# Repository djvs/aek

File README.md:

# aek[2]

USB/QMK atmega32u4 pcb for M0115, M3501 and possibly others, with WS2812B addressable LED support.  

Released without warranty, use at your own risk.  

PRs & feedback welcome!

---

Dimensions: 437.896 x 141.732 mm

---

Keyboard-Layout-Editor of Matrix for Vial: http://www.keyboard-layout-editor.com/#/gists/c7bd3d0e6c43f816d1fdc86e6fad2cfd

Default keymap: 

In Vial:

Some Photos:

Shield: [![CC BY-SA 4.0][cc-by-sa-shield]][cc-by-sa]

This work is licensed under a
[Creative Commons Attribution-ShareAlike 4.0 International License][cc-by-sa].

[![CC BY-SA 4.0][cc-by-sa-image]][cc-by-sa]

[cc-by-sa]: http://creativecommons.org/licenses/by-sa/4.0/
[cc-by-sa-image]: https://licensebuttons.net/l/by-sa/4.0/88x31.png
[cc-by-sa-shield]: https://img.shields.io/badge/License-CC%20BY--SA%204.0-lightgrey.svg

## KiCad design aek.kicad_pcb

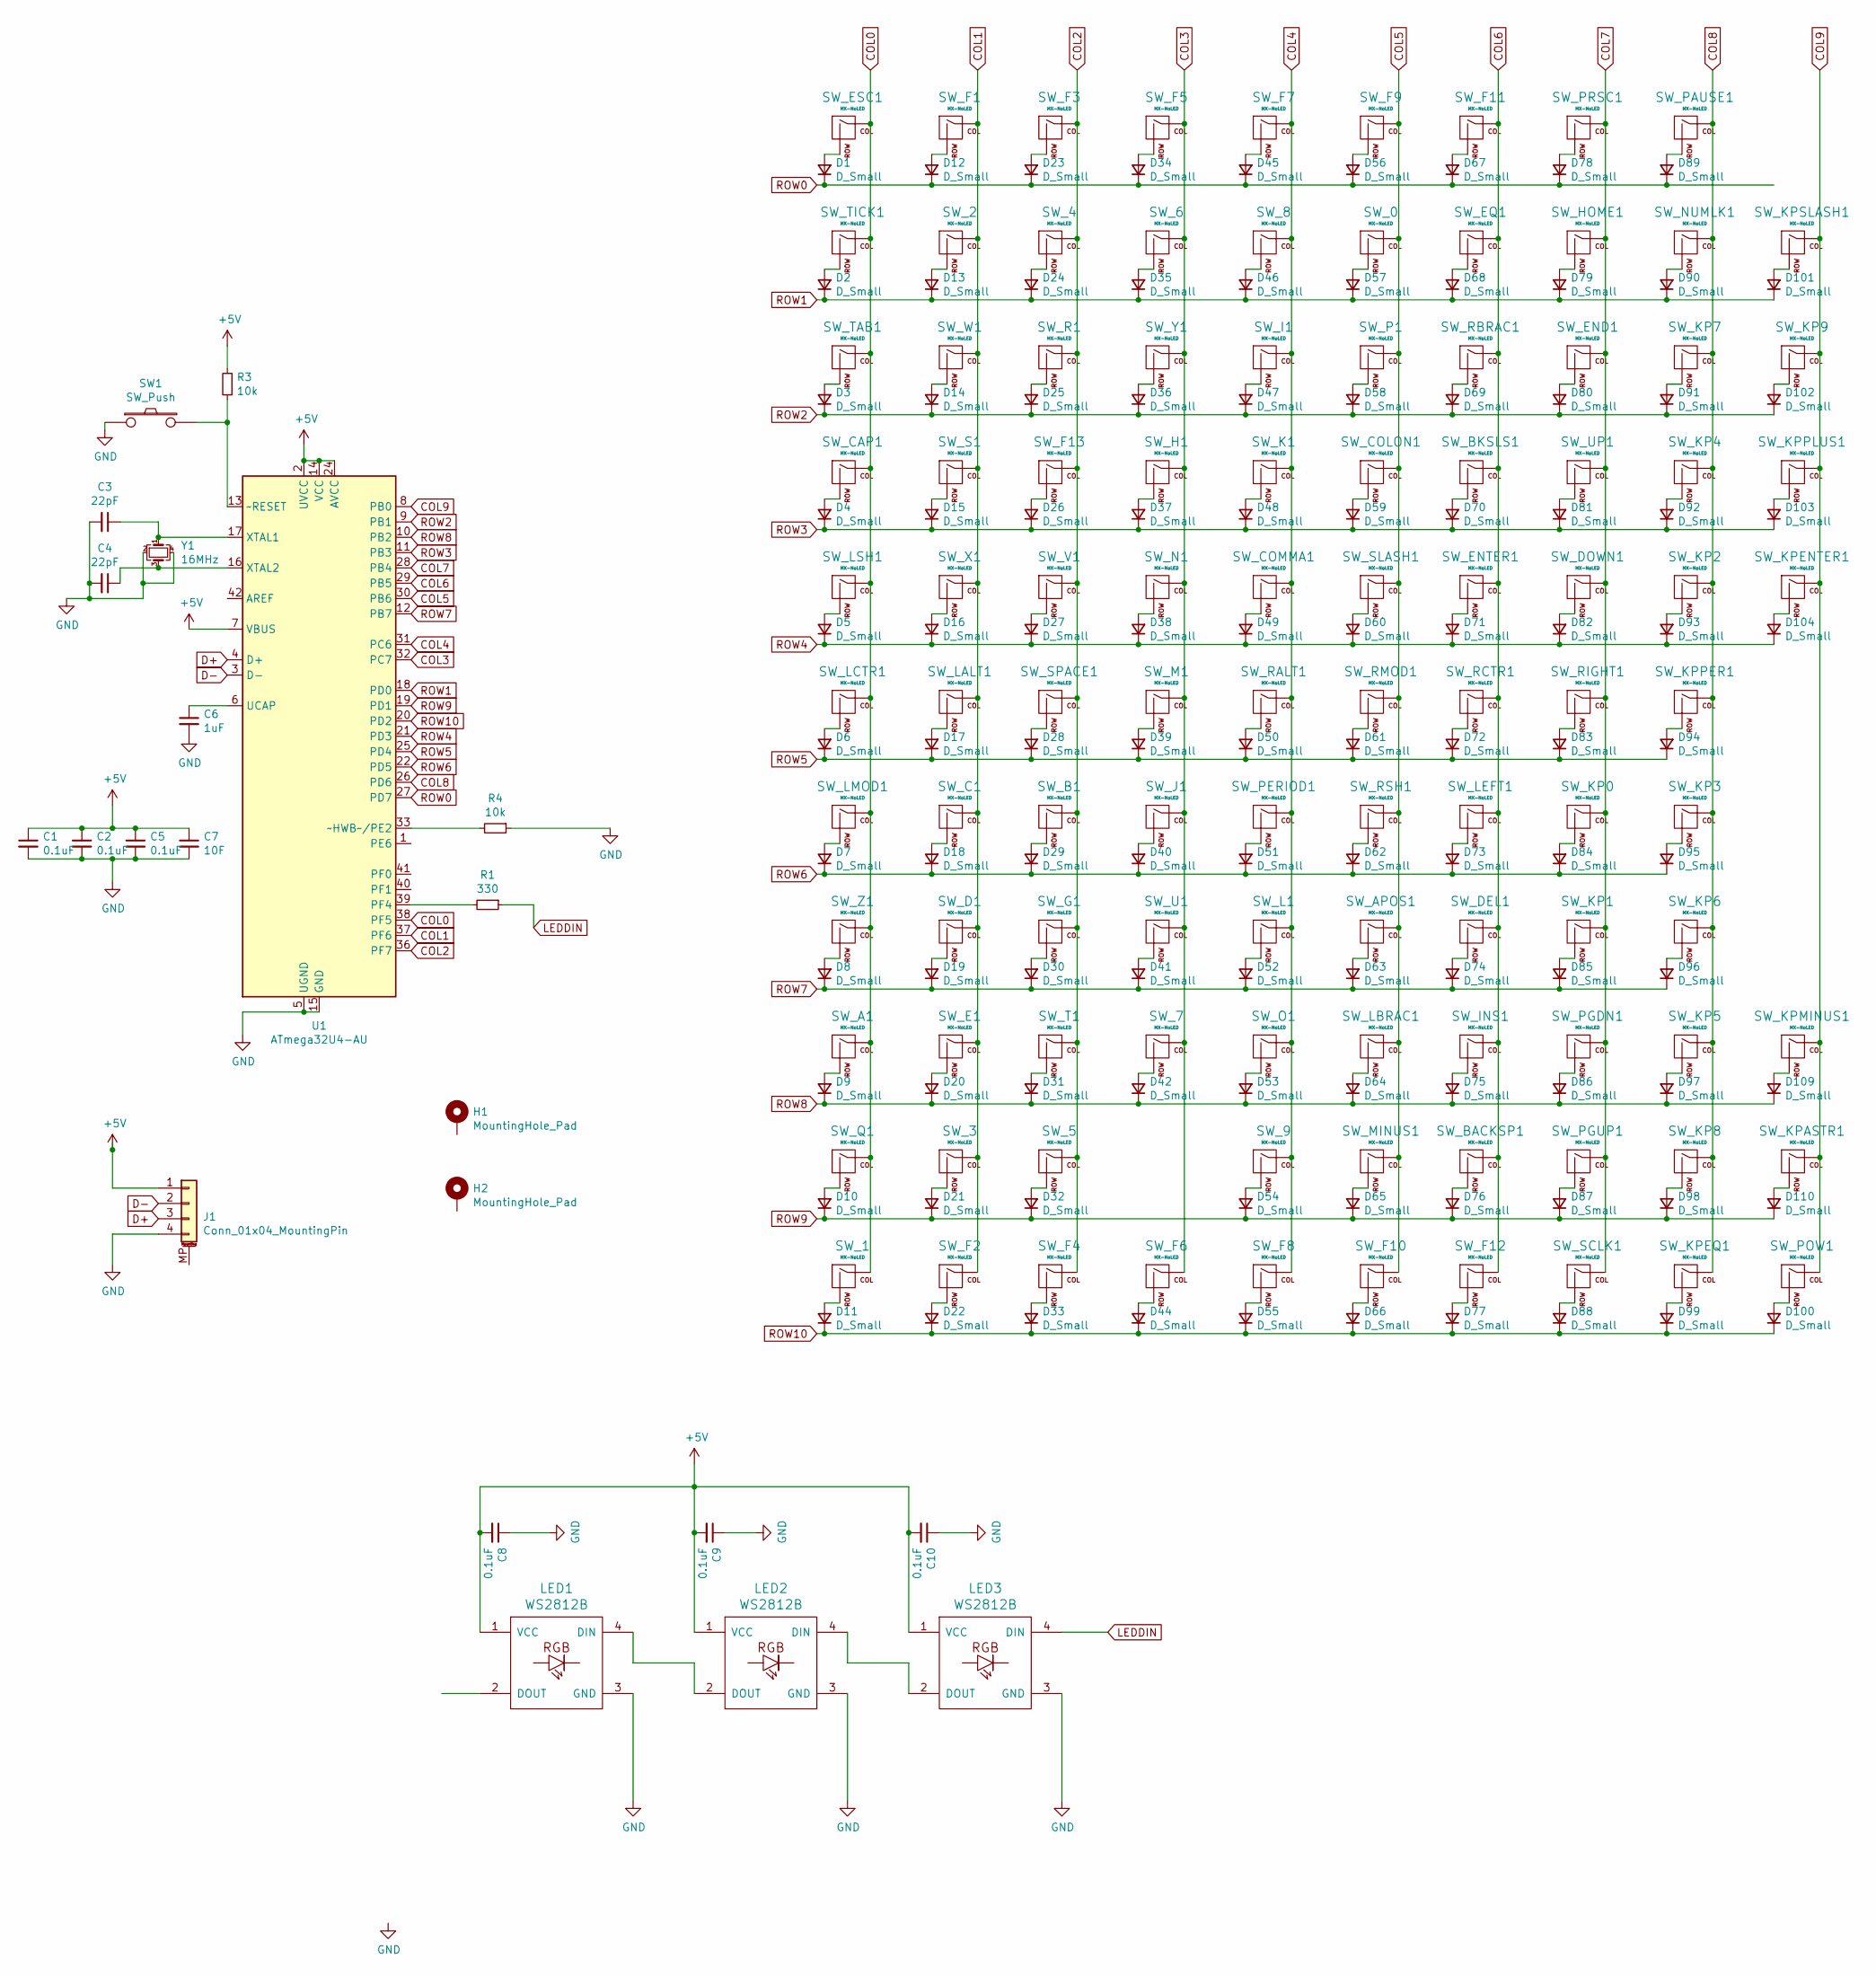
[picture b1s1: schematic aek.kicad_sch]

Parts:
C1, C2, C5, C8, C9, C10: 0.1uF; C_0805_2012Metric
C3, C4: 22pF; C_0805_2012Metric
C6: 1uF; C_0805_2012Metric
C7: 10F; C_0805_2012Metric
D1, D2, D3, D4, D5, D6, D7, D8, D9, D10, D11, D12, D13, D14, D15, D16, D17, D18, D19, D20, D21, D22, D23, D24, D25, D26, D27, D28, D29, D30, D31, D32, D33, D34, D35, D36, D37, D38, D39, D40, D41, D42, D44, D45, D46, D47, D48, D49, D50, D51, D52, D53, D54, D55, D56, D57, D58, D59, D60, D61, D62, D63, D64, D65, D66, D67, D68, D69, D70, D71, D72, D73, D74, D75, D76, D77, D78, D79, D80, D81, D82, D83, D84, D85, D86, D87, D88, D89, D90, D91, D92, D93, D94, D95, D96, D97, D98, D99, D100, D101, D102, D103, D104, D109, D110: D_Small; D_SOD-123
H1, H2: MountingHole_Pad; MountingHole_2.7mm_M2.5_Pad
J1: Conn_01x04_MountingPin; JST_SH_SM04B-SRSS-TB_1x04-1MP_P1.00mm_Horizontal
LED1, LED2, LED3: WS2812B; LED_WS2812B_PLCC4_5.0x5.0mm_P3.2mm
R1: 330; R_0805_2012Metric
R3, R4: 10k; R_0805_2012Metric
SW1: SW_Push; SKQG-1155865
SW_0, SW_1, SW_2, SW_3, SW_4, SW_5, SW_6, SW_7, SW_8, SW_9: MX-NoLED; MX-1U-NoLED
SW_A1: MX-NoLED; MX-1U-NoLED
SW_APOS1: MX-NoLED; MX-1U-NoLED
SW_B1: MX-NoLED; MX-1U-NoLED
SW_BACKSP1: MX-NoLED; MX-2U-NoLED
SW_BKSLS1: MX-NoLED; MX-1.5U-NoLED
SW_C1: MX-NoLED; MX-1U-NoLED
SW_CAP1: MX-NoLED; MX-1.75U-NoLED
SW_COLON1: MX-NoLED; MX-1U-NoLED
SW_COMMA1: MX-NoLED; MX-1U-NoLED
SW_D1: MX-NoLED; MX-1U-NoLED
SW_DEL1: MX-NoLED; MX-1U-NoLED
SW_DOWN1: MX-NoLED; MX-1U-NoLED
SW_E1: MX-NoLED; MX-1U-NoLED
SW_END1: MX-NoLED; MX-1U-NoLED
SW_ENTER1: MX-NoLED; MX-2.25U-NoLED
SW_EQ1: MX-NoLED; MX-1U-NoLED
SW_ESC1: MX-NoLED; MX-1U-NoLED
SW_F1, SW_F2, SW_F3, SW_F4, SW_F5, SW_F6, SW_F7, SW_F8, SW_F9, SW_F10, SW_F11, SW_F12, SW_F13: MX-NoLED; MX-1U-NoLED
SW_G1: MX-NoLED; MX-1U-NoLED
SW_H1: MX-NoLED; MX-1U-NoLED
SW_HOME1: MX-NoLED; MX-1U-NoLED
SW_I1: MX-NoLED; MX-1U-NoLED
SW_INS1: MX-NoLED; MX-1U-NoLED
SW_J1: MX-NoLED; MX-1U-NoLED
SW_K1: MX-NoLED; MX-1U-NoLED
SW_KP0: MX-NoLED; MX-2U-ReversedStabilizers-NoLED
SW_KP1, SW_KP2, SW_KP3, SW_KP4, SW_KP5, SW_KP6, SW_KP7, SW_KP8, SW_KP9: MX-NoLED; MX-1U-NoLED
SW_KPASTR1: MX-NoLED; MX-1U-NoLED
SW_KPENTER1: MX-NoLED; MX-2U-NoLED
SW_KPEQ1: MX-NoLED; MX-1U-NoLED
SW_KPMINUS1: MX-NoLED; MX-1U-NoLED
SW_KPPER1: MX-NoLED; MX-1U-NoLED
SW_KPPLUS1: MX-NoLED; MX-1U-NoLED
SW_KPSLASH1: MX-NoLED; MX-1U-NoLED
SW_L1: MX-NoLED; MX-1U-NoLED
SW_LALT1: MX-NoLED; MX-1.5U-NoLED
SW_LBRAC1: MX-NoLED; MX-1U-NoLED
SW_LCTR1: MX-NoLED; MX-1.5U-NoLED
SW_LEFT1: MX-NoLED; MX-1U-NoLED
SW_LMOD1: MX-NoLED; MX-1.25U-NoLED
SW_LSH1: MX-NoLED; MX-2.25U-NoLED
SW_M1: MX-NoLED; MX-1U-NoLED
SW_MINUS1: MX-NoLED; MX-1U-NoLED
SW_N1: MX-NoLED; MX-1U-NoLED
SW_NUMLK1: MX-NoLED; MX-1U-NoLED
SW_O1: MX-NoLED; MX-1U-NoLED
SW_P1: MX-NoLED; MX-1U-NoLED
SW_PAUSE1: MX-NoLED; MX-1U-NoLED
SW_PERIOD1: MX-NoLED; MX-1U-NoLED
SW_PGDN1: MX-NoLED; MX-1U-NoLED
SW_PGUP1: MX-NoLED; MX-1U-NoLED
SW_POW1: MX-NoLED; MX-1U-NoLED
SW_PRSC1: MX-NoLED; MX-1U-NoLED
SW_Q1: MX-NoLED; MX-1U-NoLED
SW_R1: MX-NoLED; MX-1U-NoLED
SW_RALT1: MX-NoLED; MX-1.5U-NoLED
SW_RBRAC1: MX-NoLED; MX-1U-NoLED
SW_RCTR1: MX-NoLED; MX-1.5U-NoLED
SW_RIGHT1: MX-NoLED; MX-1U-NoLED
SW_RMOD1: MX-NoLED; MX-1.25U-NoLED
SW_RSH1: MX-NoLED; MX-2.75U-NoLED
SW_S1: MX-NoLED; MX-1U-NoLED
SW_SCLK1: MX-NoLED; MX-1U-NoLED
SW_SLASH1: MX-NoLED; MX-1U-NoLED
SW_SPACE1: MX-NoLED; MX-6.5U-ReversedStabilizers-NoLED
SW_T1: MX-NoLED; MX-1U-NoLED
SW_TAB1: MX-NoLED; MX-1.5U-NoLED
SW_TICK1: MX-NoLED; MX-1U-NoLED
SW_U1: MX-NoLED; MX-1U-NoLED
SW_UP1: MX-NoLED; MX-1U-NoLED
SW_V1: MX-NoLED; MX-1U-NoLED
SW_W1: MX-NoLED; MX-1U-NoLED
SW_X1: MX-NoLED; MX-1U-NoLED
SW_Y1: MX-NoLED; MX-1U-NoLED
SW_Z1: MX-NoLED; MX-1U-NoLED
U1: ATmega32U4-AU; TQFP-44_10x10mm_P0.8mm
Y1: 16MHz; Crystal_SMD_3225-4Pin_3.2x2.5mm

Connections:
+5V: C1.1, C2.1, C5.1, C7.1, C8.2, C9.2, C10.2, J1.1, LED1.1 (VCC), LED2.1 (VCC), LED3.1 (VCC), R3.2, U1.2 (UVCC), U1.7 (VBUS), U1.14 (VCC), U1.24 (AVCC), U1.34 (VCC), U1.44 (AVCC)
COL0: SW_1.1 (COL), SW_A1.1 (COL), SW_CAP1.1 (COL), SW_ESC1.1 (COL), SW_LCTR1.1 (COL), SW_LMOD1.1 (COL), SW_LSH1.1 (COL), SW_Q1.1 (COL), SW_TAB1.1 (COL), SW_TICK1.1 (COL), SW_Z1.1 (COL), U1.38 (PF5)
COL1: SW_2.1 (COL), SW_3.1 (COL), SW_C1.1 (COL), SW_D1.1 (COL), SW_E1.1 (COL), SW_F1.1 (COL), SW_F2.1 (COL), SW_LALT1.1 (COL), SW_S1.1 (COL), SW_W1.1 (COL), SW_X1.1 (COL), U1.37 (PF6)
COL2: SW_4.1 (COL), SW_5.1 (COL), SW_B1.1 (COL), SW_F3.1 (COL), SW_F4.1 (COL), SW_F13.1 (COL), SW_G1.1 (COL), SW_R1.1 (COL), SW_SPACE1.1 (COL), SW_T1.1 (COL), SW_V1.1 (COL), U1.36 (PF7)
COL3: SW_6.1 (COL), SW_7.1 (COL), SW_F5.1 (COL), SW_F6.1 (COL), SW_H1.1 (COL), SW_J1.1 (COL), SW_M1.1 (COL), SW_N1.1 (COL), SW_U1.1 (COL), SW_Y1.1 (COL), U1.32 (PC7)
COL4: SW_8.1 (COL), SW_9.1 (COL), SW_COMMA1.1 (COL), SW_F7.1 (COL), SW_F8.1 (COL), SW_I1.1 (COL), SW_K1.1 (COL), SW_L1.1 (COL), SW_O1.1 (COL), SW_PERIOD1.1 (COL), SW_RALT1.1 (COL), U1.31 (PC6)
COL5: SW_0.1 (COL), SW_APOS1.1 (COL), SW_COLON1.1 (COL), SW_F9.1 (COL), SW_F10.1 (COL), SW_LBRAC1.1 (COL), SW_MINUS1.1 (COL), SW_P1.1 (COL), SW_RMOD1.1 (COL), SW_RSH1.1 (COL), SW_SLASH1.1 (COL), U1.30 (PB6)
COL6: SW_BACKSP1.1 (COL), SW_BKSLS1.1 (COL), SW_DEL1.1 (COL), SW_ENTER1.1 (COL), SW_EQ1.1 (COL), SW_F11.1 (COL), SW_F12.1 (COL), SW_INS1.1 (COL), SW_LEFT1.1 (COL), SW_RBRAC1.1 (COL), SW_RCTR1.1 (COL), U1.29 (PB5)
COL7: SW_DOWN1.1 (COL), SW_END1.1 (COL), SW_HOME1.1 (COL), SW_KP0.1 (COL), SW_KP1.1 (COL), SW_PGDN1.1 (COL), SW_PGUP1.1 (COL), SW_PRSC1.1 (COL), SW_RIGHT1.1 (COL), SW_SCLK1.1 (COL), SW_UP1.1 (COL), U1.28 (PB4)
COL8: SW_KP2.1 (COL), SW_KP3.1 (COL), SW_KP4.1 (COL), SW_KP5.1 (COL), SW_KP6.1 (COL), SW_KP7.1 (COL), SW_KP8.1 (COL), SW_KPEQ1.1 (COL), SW_KPPER1.1 (COL), SW_NUMLK1.1 (COL), SW_PAUSE1.1 (COL), U1.26 (PD6)
COL9: SW_KP9.1 (COL), SW_KPASTR1.1 (COL), SW_KPENTER1.1 (COL), SW_KPMINUS1.1 (COL), SW_KPPLUS1.1 (COL), SW_KPSLASH1.1 (COL), SW_POW1.1 (COL), U1.8 (PB0)
D+: J1.3, U1.4 (D+)
D-: J1.2, U1.3 (D-)
GND: C1.2, C2.2, C3.2, C4.2, C5.2, C6.2, C7.2, C8.1, C9.1, C10.1, J1.4, LED1.3 (GND), LED2.3 (GND), LED3.3 (GND), R4.1, SW1.1, U1.5 (UGND), U1.15 (GND), U1.23 (GND), U1.35 (GND), U1.43 (GND), Y1.2, Y1.4
LEDDIN: LED3.4 (DIN), R1.1
unnamed: C3.1, U1.17 (XTAL1), Y1.1
unnamed: C4.1, U1.16 (XTAL2), Y1.3
unnamed: C6.1, U1.6 (UCAP)
unnamed: D1.2 (A), SW_ESC1.2 (ROW)
unnamed: D2.2 (A), SW_TICK1.2 (ROW)
unnamed: D3.2 (A), SW_TAB1.2 (ROW)
unnamed: D4.2 (A), SW_CAP1.2 (ROW)
unnamed: D5.2 (A), SW_LSH1.2 (ROW)
unnamed: D6.2 (A), SW_LCTR1.2 (ROW)
unnamed: D7.2 (A), SW_LMOD1.2 (ROW)
unnamed: D8.2 (A), SW_Z1.2 (ROW)
unnamed: D9.2 (A), SW_A1.2 (ROW)
unnamed: D10.2 (A), SW_Q1.2 (ROW)
unnamed: D11.2 (A), SW_1.2 (ROW)
unnamed: D12.2 (A), SW_F1.2 (ROW)
unnamed: D13.2 (A), SW_2.2 (ROW)
unnamed: D14.2 (A), SW_W1.2 (ROW)
unnamed: D15.2 (A), SW_S1.2 (ROW)
unnamed: D16.2 (A), SW_X1.2 (ROW)
unnamed: D17.2 (A), SW_LALT1.2 (ROW)
unnamed: D18.2 (A), SW_C1.2 (ROW)
unnamed: D19.2 (A), SW_D1.2 (ROW)
unnamed: D20.2 (A), SW_E1.2 (ROW)
unnamed: D21.2 (A), SW_3.2 (ROW)
unnamed: D22.2 (A), SW_F2.2 (ROW)
unnamed: D23.2 (A), SW_F3.2 (ROW)
unnamed: D24.2 (A), SW_4.2 (ROW)
unnamed: D25.2 (A), SW_R1.2 (ROW)
unnamed: D26.2 (A), SW_F13.2 (ROW)
unnamed: D27.2 (A), SW_V1.2 (ROW)
unnamed: D28.2 (A), SW_SPACE1.2 (ROW)
unnamed: D29.2 (A), SW_B1.2 (ROW)
unnamed: D30.2 (A), SW_G1.2 (ROW)
unnamed: D31.2 (A), SW_T1.2 (ROW)
unnamed: D32.2 (A), SW_5.2 (ROW)
unnamed: D33.2 (A), SW_F4.2 (ROW)
unnamed: D34.2 (A), SW_F5.2 (ROW)
unnamed: D35.2 (A), SW_6.2 (ROW)
unnamed: D36.2 (A), SW_Y1.2 (ROW)
unnamed: D37.2 (A), SW_H1.2 (ROW)
unnamed: D38.2 (A), SW_N1.2 (ROW)
unnamed: D39.2 (A), SW_M1.2 (ROW)
unnamed: D40.2 (A), SW_J1.2 (ROW)
unnamed: D41.2 (A), SW_U1.2 (ROW)
unnamed: D42.2 (A), SW_7.2 (ROW)
unnamed: D44.2 (A), SW_F6.2 (ROW)
unnamed: D45.2 (A), SW_F7.2 (ROW)
unnamed: D46.2 (A), SW_8.2 (ROW)
unnamed: D47.2 (A), SW_I1.2 (ROW)
unnamed: D48.2 (A), SW_K1.2 (ROW)
unnamed: D49.2 (A), SW_COMMA1.2 (ROW)
unnamed: D50.2 (A), SW_RALT1.2 (ROW)
unnamed: D51.2 (A), SW_PERIOD1.2 (ROW)
unnamed: D52.2 (A), SW_L1.2 (ROW)
unnamed: D53.2 (A), SW_O1.2 (ROW)
unnamed: D54.2 (A), SW_9.2 (ROW)
unnamed: D55.2 (A), SW_F8.2 (ROW)
unnamed: D56.2 (A), SW_F9.2 (ROW)
unnamed: D57.2 (A), SW_0.2 (ROW)
unnamed: D58.2 (A), SW_P1.2 (ROW)
unnamed: D59.2 (A), SW_COLON1.2 (ROW)
unnamed: D60.2 (A), SW_SLASH1.2 (ROW)
unnamed: D61.2 (A), SW_RMOD1.2 (ROW)
unnamed: D62.2 (A), SW_RSH1.2 (ROW)
unnamed: D63.2 (A), SW_APOS1.2 (ROW)
unnamed: D64.2 (A), SW_LBRAC1.2 (ROW)
unnamed: D65.2 (A), SW_MINUS1.2 (ROW)
unnamed: D66.2 (A), SW_F10.2 (ROW)
unnamed: D67.2 (A), SW_F11.2 (ROW)
unnamed: D68.2 (A), SW_EQ1.2 (ROW)
unnamed: D69.2 (A), SW_RBRAC1.2 (ROW)
unnamed: D70.2 (A), SW_BKSLS1.2 (ROW)
unnamed: D71.2 (A), SW_ENTER1.2 (ROW)
unnamed: D72.2 (A), SW_RCTR1.2 (ROW)
unnamed: D73.2 (A), SW_LEFT1.2 (ROW)
unnamed: D74.2 (A), SW_DEL1.2 (ROW)
unnamed: D75.2 (A), SW_INS1.2 (ROW)
unnamed: D76.2 (A), SW_BACKSP1.2 (ROW)
unnamed: D77.2 (A), SW_F12.2 (ROW)
unnamed: D78.2 (A), SW_PRSC1.2 (ROW)
unnamed: D79.2 (A), SW_HOME1.2 (ROW)
unnamed: D80.2 (A), SW_END1.2 (ROW)
unnamed: D81.2 (A), SW_UP1.2 (ROW)
unnamed: D82.2 (A), SW_DOWN1.2 (ROW)
unnamed: D83.2 (A), SW_RIGHT1.2 (ROW)
unnamed: D84.2 (A), SW_KP0.2 (ROW)
unnamed: D85.2 (A), SW_KP1.2 (ROW)
unnamed: D86.2 (A), SW_PGDN1.2 (ROW)
unnamed: D87.2 (A), SW_PGUP1.2 (ROW)
unnamed: D88.2 (A), SW_SCLK1.2 (ROW)
unnamed: D89.2 (A), SW_PAUSE1.2 (ROW)
unnamed: D90.2 (A), SW_NUMLK1.2 (ROW)
unnamed: D91.2 (A), SW_KP7.2 (ROW)
unnamed: D92.2 (A), SW_KP4.2 (ROW)
unnamed: D93.2 (A), SW_KP2.2 (ROW)
unnamed: D94.2 (A), SW_KPPER1.2 (ROW)
unnamed: D95.2 (A), SW_KP3.2 (ROW)
unnamed: D96.2 (A), SW_KP6.2 (ROW)
unnamed: D97.2 (A), SW_KP5.2 (ROW)
unnamed: D98.2 (A), SW_KP8.2 (ROW)
unnamed: D99.2 (A), SW_KPEQ1.2 (ROW)
unnamed: D100.2 (A), SW_POW1.2 (ROW)
unnamed: D101.2 (A), SW_KPSLASH1.2 (ROW)
unnamed: D102.2 (A), SW_KP9.2 (ROW)
unnamed: D103.2 (A), SW_KPPLUS1.2 (ROW)
unnamed: D104.2 (A), SW_KPENTER1.2 (ROW)
unnamed: D109.2 (A), SW_KPMINUS1.2 (ROW)
unnamed: D110.2 (A), SW_KPASTR1.2 (ROW)
unnamed: LED1.4 (DIN), LED2.2 (DOUT)
unnamed: LED2.4 (DIN), LED3.2 (DOUT)
unnamed: R1.2, U1.39 (PF4)
unnamed: R3.1, SW1.2, U1.13 (~RESET)
unnamed: R4.2, U1.33 (~HWB~/PE2)
ROW0: D1.1 (K), D12.1 (K), D23.1 (K), D34.1 (K), D45.1 (K), D56.1 (K), D67.1 (K), D78.1 (K), D89.1 (K), U1.27 (PD7)
ROW1: D2.1 (K), D13.1 (K), D24.1 (K), D35.1 (K), D46.1 (K), D57.1 (K), D68.1 (K), D79.1 (K), D90.1 (K), D101.1 (K), U1.18 (PD0)
ROW2: D3.1 (K), D14.1 (K), D25.1 (K), D36.1 (K), D47.1 (K), D58.1 (K), D69.1 (K), D80.1 (K), D91.1 (K), D102.1 (K), U1.9 (PB1)
ROW3: D4.1 (K), D15.1 (K), D26.1 (K), D37.1 (K), D48.1 (K), D59.1 (K), D70.1 (K), D81.1 (K), D92.1 (K), D103.1 (K), U1.11 (PB3)
ROW4: D5.1 (K), D16.1 (K), D27.1 (K), D38.1 (K), D49.1 (K), D60.1 (K), D71.1 (K), D82.1 (K), D93.1 (K), D104.1 (K), U1.21 (PD3)
ROW5: D6.1 (K), D17.1 (K), D28.1 (K), D39.1 (K), D50.1 (K), D61.1 (K), D72.1 (K), D83.1 (K), D94.1 (K), U1.25 (PD4)
ROW6: D7.1 (K), D18.1 (K), D29.1 (K), D40.1 (K), D51.1 (K), D62.1 (K), D73.1 (K), D84.1 (K), D95.1 (K), U1.22 (PD5)
ROW7: D8.1 (K), D19.1 (K), D30.1 (K), D41.1 (K), D52.1 (K), D63.1 (K), D74.1 (K), D85.1 (K), D96.1 (K), U1.12 (PB7)
ROW8: D9.1 (K), D20.1 (K), D31.1 (K), D42.1 (K), D53.1 (K), D64.1 (K), D75.1 (K), D86.1 (K), D97.1 (K), D109.1 (K), U1.10 (PB2)
ROW9: D10.1 (K), D21.1 (K), D32.1 (K), D54.1 (K), D65.1 (K), D76.1 (K), D87.1 (K), D98.1 (K), D110.1 (K), U1.19 (PD1)
ROW10: D11.1 (K), D22.1 (K), D33.1 (K), D44.1 (K), D55.1 (K), D66.1 (K), D77.1 (K), D88.1 (K), D99.1 (K), D100.1 (K), U1.20 (PD2)

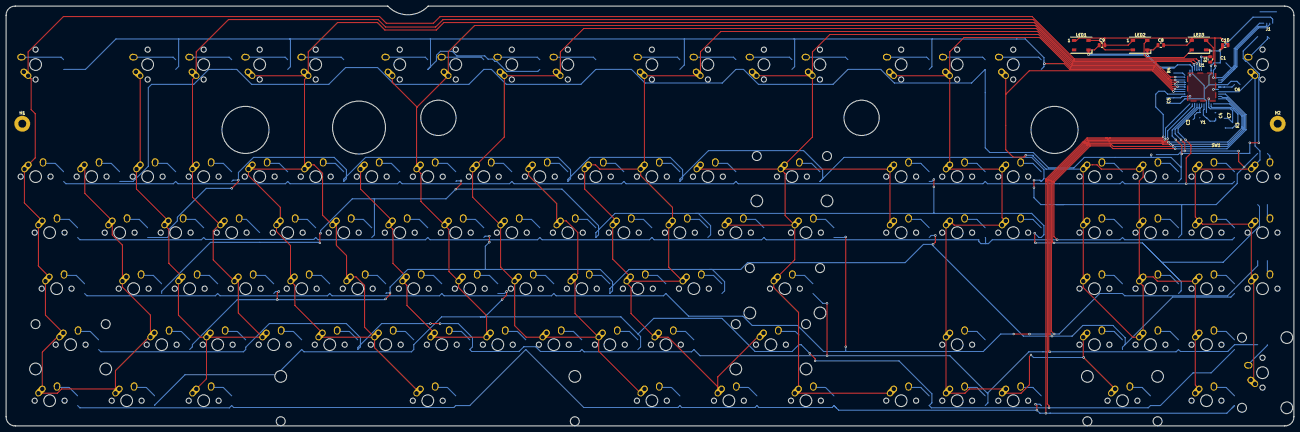
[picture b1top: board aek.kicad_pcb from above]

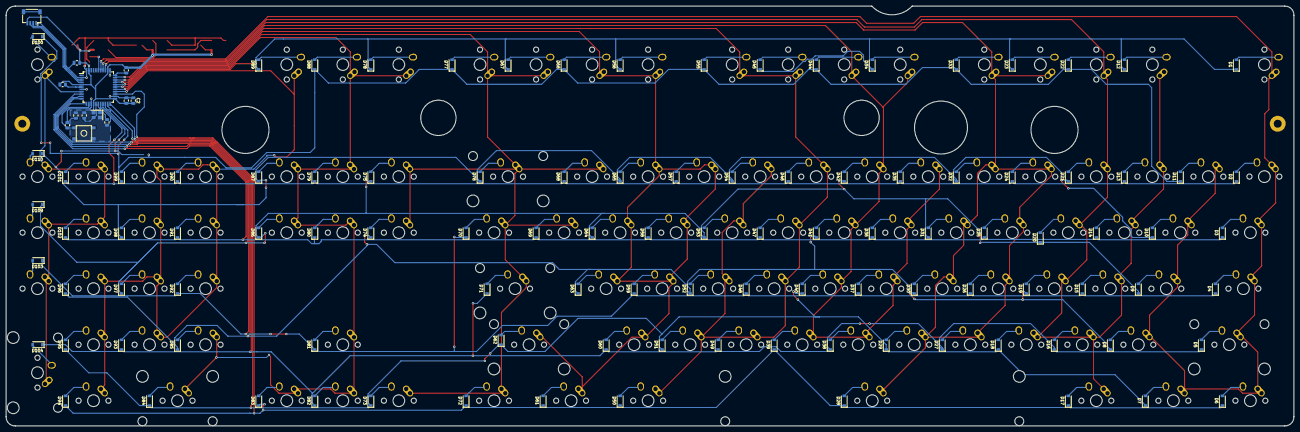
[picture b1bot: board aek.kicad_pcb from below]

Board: 2 copper layers, 437.9 x 142.7 mm, 232 parts (118 on the bottom side), 139 nets.

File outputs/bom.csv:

"Id";"Designator";"Package";"Quantity";"Designation";"Supplier and ref";
1;"R1";"R_0805_2012Metric";1;"330";;;
2;"LED3,LED2,LED1";"LED_WS2812B_PLCC4_5.0x5.0mm_P3.2mm";3;"WS2812B";;;
3;"C10,C9,C8,C5,C2,C1";"C_0805_2012Metric";6;"0.1uF";;;
4;"H1,H2";"MountingHole_2.7mm_M2.5_Pad";2;"MountingHole_Pad";;;
5;"SW_F2,SW_Z1,SW_Y1,SW_X1,SW_W1,SW_V1,SW_UP1,SW_U1,SW_TICK1,SW_T1,SW_SLASH1,SW_SCLK1,SW_S1,SW_RIGHT1,SW_RBRAC1,SW_R1,SW_Q1,SW_PRSC1,SW_POW1,SW_PGUP1,SW_PGDN1,SW_PERIOD1,SW_PAUSE1,SW_P1,SW_O1,SW_NUMLK1,SW_N1,SW_MINUS1,SW_M1,SW_LEFT1,SW_LBRAC1,SW_L1,SW_KPSLASH1,SW_KPPLUS1,SW_KPPER1,SW_KPMINUS1,SW_KPEQ1,SW_KPASTR1,SW_KP9,SW_KP8,SW_KP7,SW_KP6,SW_KP5,SW_KP4,SW_KP3,SW_KP2,SW_KP1,SW_K1,SW_J1,SW_INS1,SW_I1,SW_HOME1,SW_H1,SW_G1,SW_F13,SW_F12,SW_F11,SW_F10,SW_F9,SW_F8,SW_F7,SW_F6,SW_F5,SW_F4,SW_F3,SW_F1,SW_ESC1,SW_EQ1,SW_END1,SW_E1,SW_DOWN1,SW_DEL1,SW_D1,SW_COMMA1,SW_COLON1,SW_C1,SW_B1,SW_APOS1,SW_A1,SW_9,SW_8,SW_7,SW_6,SW_5,SW_4,SW_3,SW_2,SW_1,SW_0";"MX-1U-NoLED";89;"MX-NoLED";;;
6;"SW_CAP1";"MX-1.75U-NoLED";1;"MX-NoLED";;;
7;"SW1";"SKQG-1155865";1;"SW_Push";;;
8;"R3,R4";"R_0805_2012Metric";2;"10k";;;
9;"Y1";"Crystal_SMD_3225-4Pin_3.2x2.5mm";1;"16MHz";;;
10;"U1";"TQFP-44_10x10mm_P0.8mm";1;"ATmega32U4-AU";;;
11;"SW_TAB1,SW_RCTR1,SW_RALT1,SW_LCTR1,SW_LALT1,SW_BKSLS1";"MX-1.5U-NoLED";6;"MX-NoLED";;;
12;"SW_SPACE1";"MX-6.5U-NoLED";1;"MX-NoLED";;;
13;"SW_RSH1";"MX-2.75U-NoLED";1;"MX-NoLED";;;
14;"SW_RMOD1,SW_LMOD1";"MX-1.25U-NoLED";2;"MX-NoLED";;;
15;"SW_LSH1,SW_ENTER1";"MX-2.25U-NoLED";2;"MX-NoLED";;;
16;"SW_KPENTER1,SW_KP0,SW_BACKSP1";"MX-2U-NoLED";3;"MX-NoLED";;;
17;"J1";"JST_SH_SM04B-SRSS-TB_1x04-1MP_P1.00mm_Horizontal";1;"Conn_01x04_MountingPin";;;
18;"D110,D109,D104,D103,D102,D101,D100,D99,D98,D97,D96,D95,D94,D93,D92,D91,D90,D89,D88,D87,D86,D85,D84,D83,D82,D81,D80,D79,D78,D77,D76,D75,D74,D73,D72,D71,D70,D69,D68,D67,D66,D65,D64,D63,D62,D61,D60,D59,D58,D57,D56,D55,D54,D53,D52,D51,D50,D49,D48,D47,D46,D45,D44,D42,D41,D40,D39,D38,D37,D36,D35,D34,D33,D32,D31,D30,D29,D28,D27,D26,D25,D24,D23,D22,D21,D20,D19,D18,D17,D16,D15,D14,D13,D12,D11,D10,D9,D8,D7,D6,D5,D4,D3,D2,D1";"D_SOD-123";105;"D_Small";;;
19;"C7";"C_0805_2012Metric";1;"10F";;;
20;"C6";"C_0805_2012Metric";1;"1uF";;;
21;"C4,C3";"C_0805_2012Metric";2;"22pF";;;

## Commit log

2021-08-19 add submodules
2021-08-19 update footprints/symbols
2021-08-20 base matrix
2021-08-20 fix license
2021-08-20 first draft
2021-08-20 clenaup
2021-08-20 reposition mcu
2021-08-20 cleanup
2021-08-20 make more space for leds
2021-08-21 tweaks
2021-08-21 screenshot
2021-08-21 Some enhancements for djvs
2021-08-21 readme
2021-08-21 outputs v1
2021-08-21 Merge upgrade to kicad-nightly and generate outputs (#2)
    * readme
    * outputs v1
2021-08-21 misc
2021-08-22 mxplate and hacky bom/cpl outputs
2021-08-22 working mx plate
2021-08-22 mounting holes for plate
2021-08-23 extension for buzzer from PF0
2021-08-23 bom/cpl
2021-08-24 cleanup and gitignore aek-backups
2021-08-24 grid option on numpad
2021-08-24 fix schematic issue
2021-08-24 Minor enchancements in MCU area
2021-08-24 Minor enchancements in MCU area (#3)
2021-08-29 script for bom patchup
2021-09-02 update outputs and screenshot
2021-09-02 fix bom/cpl and scripts
2021-09-02 namespace bom/cpl outputs
2021-09-03 continuous ground on F.Cu and custom footprint for merged au/mu atmega32u4
2021-09-03 update screenshot
2021-09-29 bug fixes
2021-09-29 add blank firmware
2021-09-29 firmware WIP
2021-09-29 firmware id
2021-09-29 matrix
2021-09-30 reduce risk of jlcpcb diode misrotation
2021-10-01 fix matrix and keymap
2021-10-08 fix dimensions in readme
2021-10-26 cleanup & onboard AST1109MLQ
2021-10-26 Add option for through-hole LEDs and other cleanup (#6)
    * updates
    * update
    * update
2022-07-22 prep for vial
2022-07-22 added kle matrix for vial
2022-07-22 something is wrong here, ill fix it later....
2022-07-22 Update README.md
    added matrix diagrams from KLE
2022-08-04 Fixed syntax errors
2022-08-05 Added Vial support + changed POWER key to Windows Lock combo
2022-08-05 Update README.md
    added some screenshots and info about Vial
2022-08-05 Add files via upload
    Compiled hex firmware. Default and Vial Supported.
2022-08-05 Added some photos
    Added some photos
2022-08-08 fixed KC PLUS
2022-08-08 Update vial hex with correct matrix
2022-08-08 reverted changes
2022-08-08 Updates both JSON and Vial JSON
2022-08-09 Support for Vial and update QMK to remove redundant options. (#7)
    * prep for vial
    * added kle matrix for vial
    * something is wrong here, ill fix it later....
    * Update README.md
    added matrix diagrams from KLE
    * Fixed syntax errors
2023-02-26 fixes
2025-12-14 update keymaps and add custom animation
